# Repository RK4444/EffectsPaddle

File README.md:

# EffectsPaddle
A Guitar Effects Paddle

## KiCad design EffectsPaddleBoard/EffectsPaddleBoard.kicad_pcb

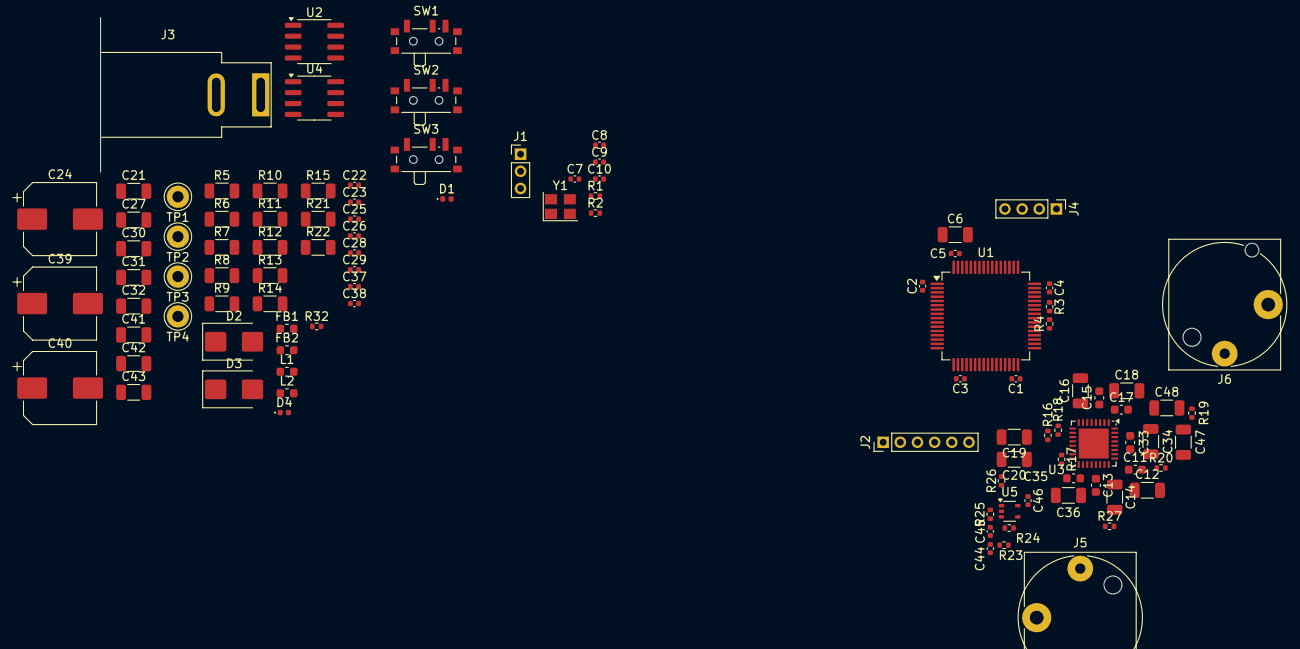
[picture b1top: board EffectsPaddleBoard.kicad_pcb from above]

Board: 4 copper layers, 107 parts (0 on the bottom side), 66 nets, no tracks yet.

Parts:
C1, C2, C3, C4, C5, C7, C8, C23, C38, C46: 100n; C_0402_1005Metric
C6, C16, C18, C21, C27, C30, C34, C36, C41: 10u; C_1206_3216Metric
C9, C10: 10p; C_0402_1005Metric
C11, C13, C15, C17, C33, C35: 100n; C_0603_1608Metric
C12, C14: 22u; C_1206_3216Metric
C19, C20, C31, C32, C42, C43, C47, C48: 1u; C_1206_3216Metric
C22, C37: 15n; C_0402_1005Metric
C24, C39, C40: 470u; CP_Elec_8x10
C25, C26, C28, C29, C44: 220p; C_0402_1005Metric
C45: 10n; C_0402_1005Metric
D1, D4: LED; LED_0402_1005Metric
D2, D3: B230; D_SMB
FB1, FB2: 600; L_0603_1608Metric
H1, H2, H3, H4: MountingHole; MountingHole_3.2mm_M3
J1: Conn_01x03_Pin; PinHeader_1x03_P2.00mm_Vertical
J2: Conn_01x06_Pin; PinHeader_1x06_P2.00mm_Vertical
J3: Barrel_Jack; BarrelJack_SwitchcraftConxall_RAPC10U_Horizontal
J4: Conn_01x04_Pin; PinHeader_1x04_P2.00mm_Vertical
J5, J6: AudioJack2; Jack_6.35mm_Neutrik_NJ2FD-V_Vertical
L1, L2: 15u; L_0603_1608Metric
R1, R16, R17, R18, R20, R23, R24, R25, R26, R27: 10k; R_0402_1005Metric
R2, R32: 220; R_0402_1005Metric
R3, R4: 2k2; R_0402_1005Metric
R5, R10: 332k; R_1206_3216Metric
R6, R11: 68.1k; R_1206_3216Metric
R7: 10.2k; R_1206_3216Metric
R8: 3.24k; R_1206_3216Metric
R9, R12: 30.9k; R_1206_3216Metric
R13: 10k; R_1206_3216Metric
R14, R15: 3.9k; R_1206_3216Metric
R19: 0; R_0402_1005Metric
R21: 4k7; R_1206_3216Metric
R22: 3k9; R_1206_3216Metric
SW1, SW2, SW3: SW_SPDT; SW_SPDT_PCM12
TP1, TP2, TP3, TP4: TestPoint; Pin_D1.3mm_L11.0mm
U1: STM32F405RGTx; LQFP-64_10x10mm_P0.5mm
U2, U4: TPS54233; SOIC-8_3.9x4.9mm_P1.27mm
U3: TLV320AIC3100; VQFN-32-1EP_5x5mm_P0.5mm_EP3.5x3.5mm
U5: MCP6401T-xLT; SOT-353_SC-70-5
Y1: 16MHz; Crystal_SMD_3225-4Pin_3.2x2.5mm

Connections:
+1V8: C15.1, C16.1, C40.1, R21.1, R22.2, U3.3 (DVDD)
+3.3V: C1.1, C2.1, C3.1, C4.1, C5.1, C6.1, C7.1, C17.1, C18.1, C24.1, C32.1, FB1.2, J2.1, L1.2, R3.1, R4.1, R7.1, R22.1, R32.2, SW1.1 (A), SW3.3 (C), TP1.1, U1.1 (VBAT), U1.19 (VDD), U1.32 (VDD), U1.48 (VDD), U1.64 (VDD), U3.2 (IOVDD)
+3.3VA: C30.1, C31.1, C33.1, C34.1, C35.1, C36.1, FB1.1, U1.13 (VDDA), U3.17 (AVDD), U3.28 (HPVDD)
+5V: C11.1, C12.1, C13.1, C14.1, C39.1, C43.1, FB2.2, L2.2, R13.1, TP2.1, U3.21 (SPKVDD), U3.24 (SPKVDD)
+5VA: C41.1, C42.1, C46.1, FB2.1, R24.2, U5.5 (V+)
/Analog_FrontBackend/AudioInBoard: J5.T, R23.1
/Analog_FrontBackend/InLP: C44.1, C45.1, R23.2
/Analog_FrontBackend/InSigAudio: C45.2, R24.1, R25.2, U5.3 (+)
/Barreljack_in: C21.1, C27.1, J3.1, R5.1, R10.1, U2.2 (VIN), U4.2 (VIN)
/Codec/Analog_In_L: C19.1, U3.13 (MIC1LP)
/Codec/Analog_In_R: C20.1, U3.14 (MIC1RP)
/Codec/HPCouplingLR: C48.2, R19.2
/Codec/HPL: C47.1, U3.27 (HPL)
/Codec/HPR: C48.1, U3.30 (HPR)
/Codec/HeadphonesOut: C47.2, J6.T, R19.1
/Codec/MIC1LM: R17.1, U3.15 (MIC1LM)
/Codec/MICBIAS: R16.1, U3.12 (MICBIAS)
/Codec/SPKL: R20.1, U3.22 (SPKP), U3.26 (SPKP)
/Codec/SPKR: R27.1, U3.19 (SPKM), U3.23 (SPKM)
/Codec/Volume: R18.1, U3.11 (VOL/MICDET)
/SS3v3: C22.1, U2.4 (SS)
/SS5v: C37.1, U4.4 (SS)
/b3v3: C23.1, U2.1 (BOOT)
/b5v: C38.1, U4.1 (BOOT)
/comp3v3: C25.1, C26.1, U2.6 (COMP)
/comp5v: C28.1, C29.1, U4.6 (COMP)
/en3v3: R5.2, R6.1, U2.3 (EN)
/en5v: R10.2, R11.1, U4.3 (EN)
/fb3v3: R7.2, R8.1, U2.5 (FB)
/fb5v: R13.2, R14.1, R15.1, U4.5 (FB)
/ph3v3out: C23.2, D2.1 (K), L1.1, U2.8 (PH)
/ph5vout: C38.2, D3.1 (K), L2.1, U4.8 (PH)
/uC/Boot3V3: C7.2, SW2.1 (A)
/uC/BootGND: C8.1, SW2.3 (C)
ADC11: J2.2, U1.14 (PA0)
ADC12: J2.3, U1.15 (PA1)
ADC13: J2.4, U1.16 (PA2)
ADC14: J2.5, U1.17 (PA3)
Analog_In1: C19.2, U5.1, U5.4 (-)
Analog_In2: C20.2, R26.2
Codec_GPIO: U1.23 (PA7), U3.32 (GPIO1)
Codec_Reset: SW2.2 (B), U1.7 (NRST), U3.31 (~RESET)
GND: C1.2, C2.2, C3.2, C4.2, C5.2, C6.2, C8.2, C9.2, C10.2, C11.2, C12.2, C13.2, C14.2, C15.2, C16.2, C17.2, C18.2, C21.2, C22.2, C24.2, C25.2, C27.2, C29.2, C30.2, C31.2, C32.2, C33.2, C34.2, C35.2, C36.2, C37.2, C39.2, C40.2, C41.2, C42.2, C43.2, C44.2, C46.2, D1.1 (K), D2.2 (A), D3.2 (A), D4.1 (K), J1.3, J2.6, J3.2, J5.S, J6.S, R6.2, R8.2, R9.2, R11.2, R12.2, R14.2, R15.2, R16.2, R17.2, R18.2, R20.2, R21.2, R25.1, R26.1, R27.2, SW1.3 (C), SW3.1 (A), TP3.1, TP4.1, U1.12 (VSSA), U1.18 (VSS), U1.63 (VSS), U2.7 (GND), U3.1 (IOVSS), U3.16 (AVSS), U3.18 (DVSS), U3.20 (SPKVSS), U3.25 (SPKVSS), U3.29 (HPVSS), U3.33 (EP), U4.7 (GND), U5.2 (V-), Y1.2, Y1.4
I2C_SCL: R3.2, U1.41 (PA8), U3.10 (SCL)
I2C_SDA: R4.2, U1.40 (PC9), U3.9 (SDA)
I2S_CK: U1.34 (PB13), U3.7 (BCLK)
I2S_MCK: U1.37 (PC6), U3.8 (MCLK)
I2S_SD: U1.36 (PB15), U3.5 (DIN)
I2S_WS: U1.33 (PB12), U3.6 (WCLK)
I2S_ext_SD: U1.35 (PB14), U3.4 (DOUT)
JTAG_TCK: J4.2, U1.49 (PA14)
JTAG_TDI: J4.3, U1.50 (PA15)
JTAG_TDO: J4.4, U1.55 (PB3)
JTAG_TMS: J4.1, U1.46 (PA13)
unnamed: C26.2, R9.1
unnamed: C28.2, R12.1
unnamed: D1.2 (A), R2.1
unnamed: D4.2 (A), R32.1
unnamed: R1.1, SW1.2 (B)
unnamed: R1.2, U1.60 (BOOT0)
OSC_PH0: C9.1, U1.5 (PH0), Y1.1
OSC_PH1: C10.1, U1.6 (PH1), Y1.3
On-Switch: SW3.2 (B), U1.57 (PB5)
PWR_LED_uC: R2.2, U1.58 (PB6)
UART_RX: J1.1, U1.54 (PD2)
UART_TX: J1.2, U1.53 (PC12)

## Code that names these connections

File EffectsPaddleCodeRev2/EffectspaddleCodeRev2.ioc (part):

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Mcu.Name=STM32F405RGTx
Mcu.Package=LQFP64
Mcu.UserName=STM32F405RGTx
PA0-WKUP.Signal=ADCx_IN0
PA1.Signal=ADCx_IN1
PA13.Mode=JTAG_4_pins
PA13.Signal=SYS_JTMS-SWDIO
PA14.Mode=JTAG_4_pins
PA14.Signal=SYS_JTCK-SWCLK
PA15.Mode=JTAG_4_pins
PA15.Signal=SYS_JTDI
PA2.Signal=ADCx_IN2
PA3.Signal=ADCx_IN3
PA8.Mode=I2C
PA8.Signal=I2C3_SCL
PB12.Mode=Full_Duplex_Master
PB12.Signal=I2S2_WS
PB13.Mode=Full_Duplex_Master
PB13.Signal=I2S2_CK
PB14.Mode=Full_Duplex_Master
PB14.Signal=I2S2_ext_SD
PB15.Mode=Full_Duplex_Master
PB15.Signal=I2S2_SD
PB3.Mode=JTAG_4_pins
PB3.Signal=SYS_JTDO-SWO
PB5.GPIOParameters=GPIO_Label
PB5.GPIO_Label=OnSwitch
PB5.Signal=GPIO_Input
PB6.GPIOParameters=GPIO_Label
PB6.GPIO_Label=LED
PB6.Signal=GPIO_Output
PC12.Mode=Asynchronous
PC12.Signal=UART5_TX
PC6.Mode=Master_Clock_Activated
PC6.Signal=I2S2_MCK
PC9.Mode=I2C
PC9.Signal=I2C3_SDA
PD2.Mode=Asynchronous
PD2.Signal=UART5_RX
PH0-OSC_IN.Mode=HSE-External-Oscillator
PH0-OSC_IN.Signal=RCC_OSC_IN
PH1-OSC_OUT.Mode=HSE-External-Oscillator
PH1-OSC_OUT.Signal=RCC_OSC_OUT
RCC.HSE_VALUE=16000000
RCC.SYSCLKFreq_VALUE=168000000
RCC.SYSCLKSource=RCC_SYSCLKSOURCE_PLLCLK
board=custom

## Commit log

2023-06-29 Added the chips, no routing yet
2023-06-29 Added the hardware configuration
2023-06-30 Added UART and an on off switch input
2023-06-30 Put in global identifiers in schematic
2023-07-01 Added power to uC, but overall power not finished
2023-11-28 While wiring the codec, I found that I used the wrong controller and so I2S communication is unidirectional only: TODO: fix that
2023-11-28 Made new project with right processor
2023-11-29 Added power supply
2023-12-12 Finished schematic
2023-12-22 Began with pcb layout
2023-12-27 Reviev by David and netnaming
2023-12-28 Proceeded in layout, just power is missing
2023-12-30 Finished layout
2024-01-01 Added 3d models
2024-01-05 Added netclass colours and basic routing, made small changes in reset structure
2024-01-06 Review hardware layout and add considerations about the circuit partition and components placement
2024-01-08 Tried separating analog and digital part
2024-01-08 Added note for reviewer
2024-01-23 Corrections, see comments
2024-01-24 Corrected the board, now all parts should be right
2024-01-25 Layout completed
2024-01-25 Last commit on review1
2024-01-25 Signal routing almost done
2024-01-29 Added filter simulation and last copperfills on front copper (ugly)
2024-01-31 Eliminated all except 2 DRC errors
2024-02-02 Added all parts
2024-02-05 Added final button footprint
2024-02-08 Added double buffering in firmware
2024-02-09 Added further testpoints
2024-02-13 Added better switch footprint
2024-02-14 exported symbols and footprints, updated PCB
2024-02-14 fixed manf part nr on inductor and caps
2024-02-14 Added new buck regulator, but footprint is missing
2024-02-17 Begun with double sided layout
2024-03-06 Upgraded to kicad8 and improved layout
2024-03-06 Changed oscillator, not sure if this works
2025-01-01 Started completely new layout
2025-04-12 Reworked schematic completely, design will be next, if someone knows, where my branches went, tell me
